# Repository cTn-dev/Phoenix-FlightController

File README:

Flight Controller implementation using Teensy 3.0 as "brain".

PIN setup
I2C SCL - 19
I2C SDA - 18

Rotor 1 - 22
Rotor 2 - 23
Rotor 3 - 9
Rotor 4 - 10

Orientation lights - 14
Battery monitor - 15

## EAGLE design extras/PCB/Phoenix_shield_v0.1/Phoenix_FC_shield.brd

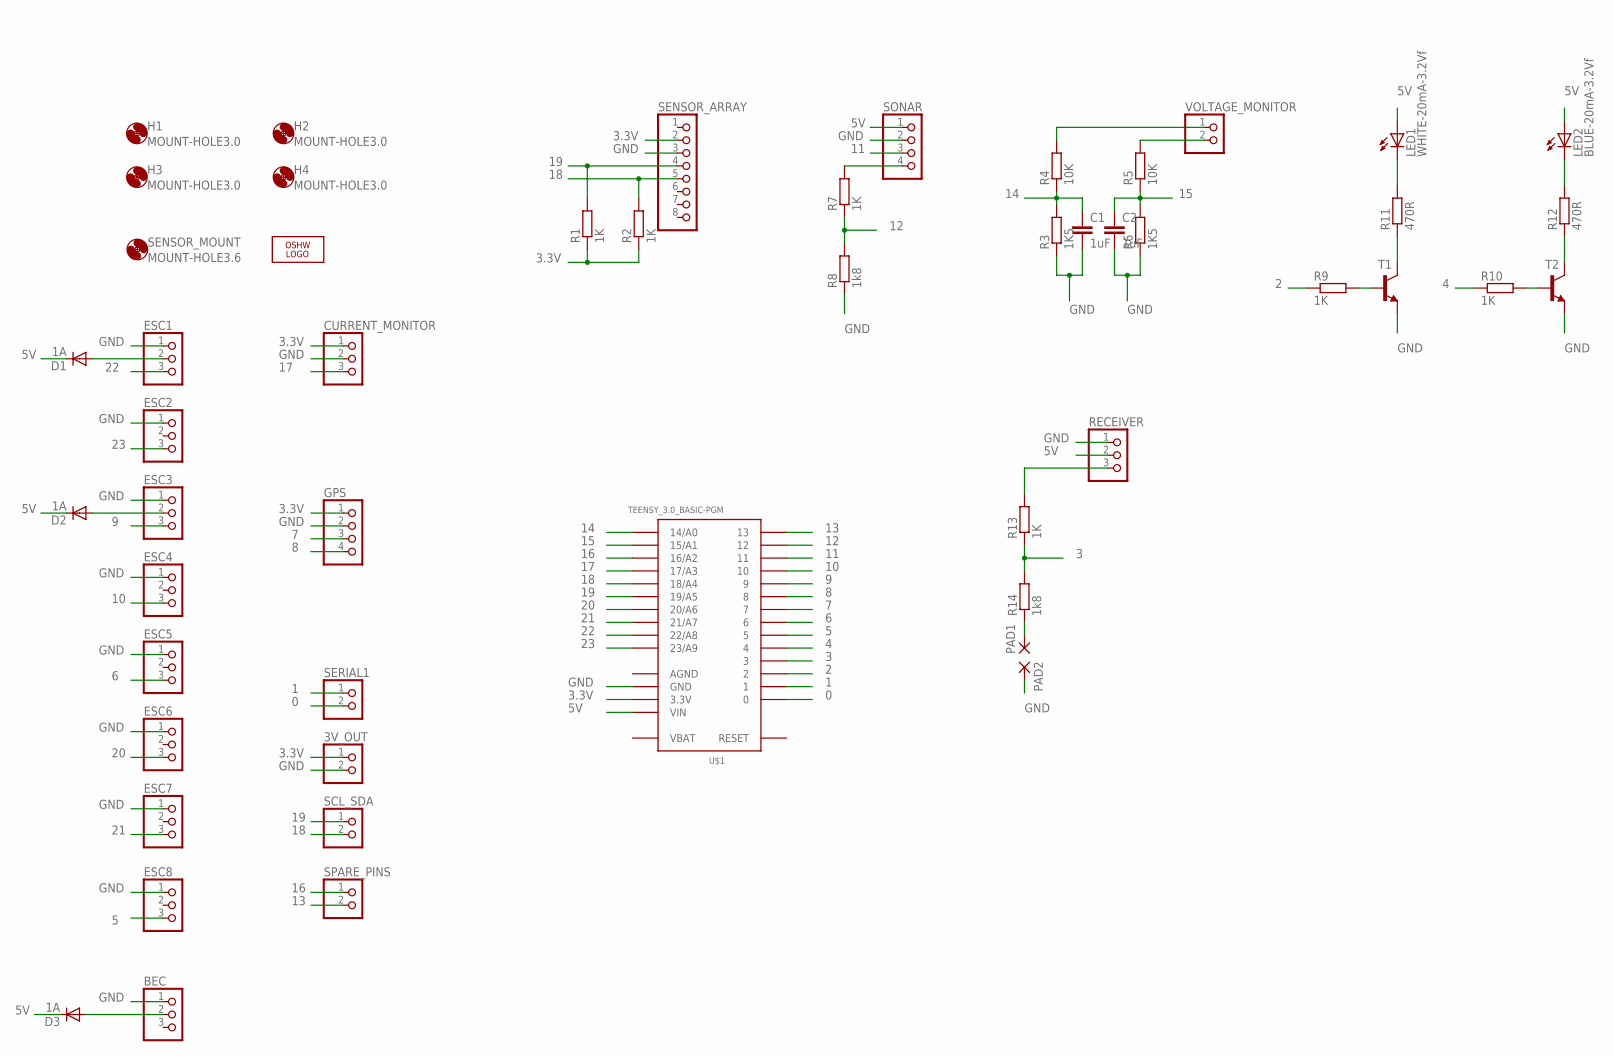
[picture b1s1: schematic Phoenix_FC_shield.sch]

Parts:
3V_OUT: PINHD-1X2; 1X02
BEC: PINHD-1X3; 1X03
C1, C2: 1uF; C0805
CURRENT_MONITOR: PINHD-1X3; 1X03
D1, D2, D3: 1A; DO-214AC
ESC1, ESC2, ESC3, ESC4, ESC5, ESC6, ESC7, ESC8: PINHD-1X3; 1X03
GPS: PINHD-1X4; 1X04
H1, H2, H3, H4: MOUNT-HOLE3.0; 3,0
LED1: WHITE-20mA-3.2Vf; CHIP-LED0805
LED2: BLUE-20mA-3.2Vf; CHIP-LED0805
LOGO1: OSHW_LOGO_8MILX0200-NT; OSHW_8X200_NOTEXT
PAD1, PAD2: WIREPADSMD1,27-254; SMD1,27-2,54
R1, R2, R7, R9, R10, R13: 1K; R0805
R3, R6: 1K5; R0805
R4, R5: 10K; R0805
R8, R14: 1k8; R0805
R11, R12: 470R; R0805
RECEIVER: PINHD-1X3; 1X03
SCL_SDA: PINHD-1X2; 1X02
SENSOR_ARRAY: PINHD-1X8; 1X08
SENSOR_MOUNT: MOUNT-HOLE3.6; 3,6
SERIAL1: PINHD-1X2; 1X02
SONAR: PINHD-1X4; 1X04
SPARE_PINS: PINHD-1X2; 1X02
T1, T2: BC817-40SMD; SOT23-BEC
U$1: TEENSY_3.0_BASIC-PGM
VOLTAGE_MONITOR: PINHD-1X2; 1X02

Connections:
0: SERIAL1.2, U$1.0
1: SERIAL1.1, U$1.1
2: R9.1, U$1.2
3: R13.1, R14.2, U$1.3
3.3V: 3V_OUT.1, CURRENT_MONITOR.1, GPS.1, R1.1, R2.1, SENSOR_ARRAY.2, U$1.3.3V, U$1.3.3V1 (3.3V)
4: R10.1, U$1.4
5: ESC8.3, U$1.5
5V: D1.C, D2.C, D3.C, LED1.A, LED2.A, RECEIVER.2, SONAR.1, U$1.VIN
6: ESC5.3, U$1.6
7: GPS.3, U$1.7
8: GPS.4, U$1.8
9: ESC3.3, U$1.9
10: ESC4.3, U$1.10
11: SONAR.3, U$1.11
12: R7.1, R8.2, U$1.12
13: SPARE_PINS.2, U$1.13
14: C1.1, R3.2, R4.1, U$1.14/A0
15: C2.1, R5.1, R6.2, U$1.15/A1
16: SPARE_PINS.1, U$1.16/A2
17: CURRENT_MONITOR.3, U$1.17/A3
18: R2.2, SCL_SDA.2, SENSOR_ARRAY.5, U$1.18/A4
19: R1.2, SCL_SDA.1, SENSOR_ARRAY.4, U$1.19/A5
20: ESC6.3, U$1.20/A6
21: ESC7.3, U$1.21/A7
22: ESC1.3, U$1.22/A8
23: ESC2.3, U$1.23/A9
AGND: U$1.AGND
GND: 3V_OUT.2, BEC.1, C1.2, C2.2, CURRENT_MONITOR.2, ESC1.1, ESC2.1, ESC3.1, ESC4.1, ESC5.1, ESC6.1, ESC7.1, ESC8.1, GPS.2, PAD2.1, R3.1, R6.1, R8.1, RECEIVER.1, SENSOR_ARRAY.3, SONAR.2, T1.E, T2.E, U$1.GND, U$1.GND1 (GND)
unnamed: R5.2, VOLTAGE_MONITOR.2
unnamed: R7.2, SONAR.4
unnamed: R11.1, T1.C
unnamed: R9.2, T1.B
unnamed: D2.A, ESC3.2
unnamed: PAD1.1, R14.1
unnamed: R4.2, VOLTAGE_MONITOR.1
unnamed: R10.2, T2.B
unnamed: R12.1, T2.C
unnamed: LED1.C, R11.2
unnamed: LED2.C, R12.2
unnamed: D1.A, ESC1.2
unnamed: R13.2, RECEIVER.3
unnamed: BEC.2, D3.A
VBAT: U$1.VBAT

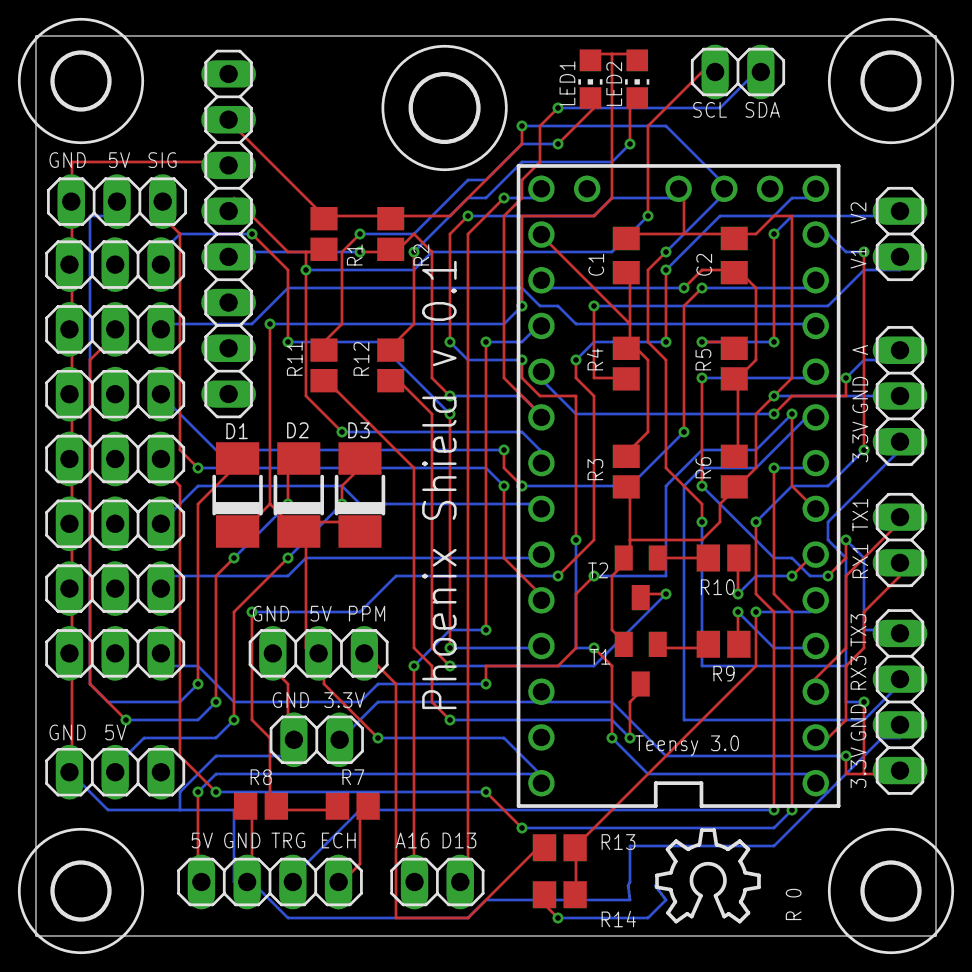
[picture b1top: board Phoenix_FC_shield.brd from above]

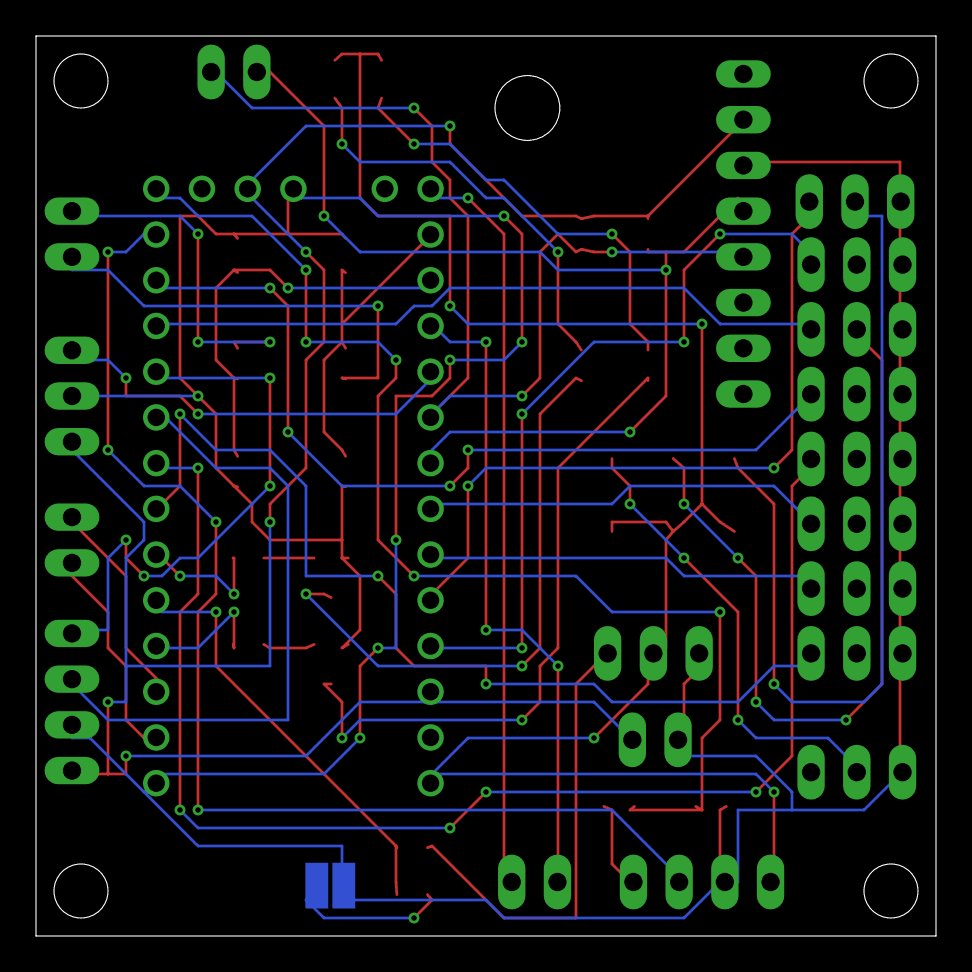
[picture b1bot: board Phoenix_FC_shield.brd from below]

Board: 2 copper layers, 50.0 x 50.0 mm, 51 parts (2 on the bottom side), 41 nets.

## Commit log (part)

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2012-12-16 auto disarm after throttle reaches 1000us (0)
2012-12-16 cleaning up
2012-12-16 more cleanup
2012-12-16 Manual accel offset calibration
2012-12-17 BIG changes to the sensor data handling
    did a rather long flight test, everything seems to be running smooth
2012-12-19 orientation lights & status support
2012-12-20 Added accel scale factor
2012-12-20 bias calculations
2012-12-20 cut off tunings
2012-12-21 readme update
2012-12-21 YAW angle build up "speed up"
2012-12-22 Battery monitor code cleanup + documentation
2012-12-22 temporary disabling battery monitor
    (till the new current sensor arrives)
2012-12-23 cleanup & YAW stick angle speed up
2012-12-23 typo fix
2012-12-24 debugging for ARG
2012-12-24 Critical Readme updates
2012-12-25 readme updates
2012-12-25 optimizations & polish
2012-12-27 optimizations
2012-12-27 mpu documentation header
2012-12-27 pre-baro changes
2012-12-27 altitude hold support
2012-12-27 throttle panic support
2012-12-28 data visualization
2012-12-28 visualization polish
    According to data visualization it seems there is still some improvement
    regarding accel fusion in kinematics
2012-12-29 Lowered accelerometer weight in CMP
2012-12-30 full support for RX visualization
2012-12-31 also output PPM_error with graph data
2013-01-03 accelerometer angle flip corrections
2013-01-03 lots of changes (in the graph area)
2013-01-04 UI polish and 3D visualization
2013-01-04 kinematicsZ PI normalization and YAW corrections
2013-01-05 differen't approach to improve sensor fusion
2013-01-06 DCM kinematics implementation
2013-01-06 YAW fixes
2013-01-06 support for hexa and octo in flex0
2013-01-08 sonar integration (untested)
2013-01-08 IMPORTANT baro and sonar fixes
2013-01-09 partial commit introducing configuration file
2013-01-09 finally dividing sensors into separate libraries
2013-01-09 motor pin setup order change (for clarity)
2013-01-10 moving rx failsafe to the main contoller file
2013-01-10 initial register support for older sensors
2013-01-10 baro/sonar PID changes
    Baro and sonar now uses different PIDs, also by disabling baro/sonar the
    PID objects are removed which helps reduce sketch size on older
    platforms
2013-01-11 new folder structure
2013-01-11 object oriented i2c sensor base
    srf04 isn't part of this sensor array
2013-01-11 improvements in the JS area
2013-01-11 YAW angle flip bugfix
2013-01-11 made the PID throttle correction range bigger
    still requires PID tuning, but its getting there
2013-01-13 PID changes @ I2C timeout testing
2013-01-14 some improvements, serial handling class tomorrow
2013-01-15 initial Ublox commit & mpu6050 i2c bypass
2013-01-16 i2c scanner in extras folder
2013-01-16 initial MS5611 sensor support (not working yet)
2013-01-17 proper HMC5883L support
2013-01-17 GPS polishing
2013-01-18 scale factor update
2013-01-19 3D visualization bugfixes
2013-01-19 full battery monitor current support
2013-01-19 accel calibration
2013-01-20 polish & optimizing
2013-01-21 new sensor data storage structure (array based)
    also all kinematics now take sensor data via priority
    gyro => accel => mag => gps = > magic genie
2013-01-21 some notes from kha
2013-01-24 ARG fixes
2013-01-26 optimization & documentation
2013-01-26 gyro calibration sanity checks
2013-01-26 multiple frames related changes
2013-01-27 ADXL345 & ITG3200 support
2013-01-27 polishing
2013-01-27 cleanup
2013-01-27 tiny cleanup
2013-01-28 bugfix
2013-01-30 faster baro response
    (this is still in testing, i am having some serious problems testing the
    baro alt hold indoors)
2013-01-30 typo fix and support for some basic OFF ON defines
2013-02-01 more EEPROM support
2013-02-01 Adding support to ACCEL on dataStorage, fixing some indentation problems on ACCEL as well. Changed dataStorage include position so it can be accessed on other included files.
2013-02-01 small type change
2013-02-01 3,4,6,8 motor setup for teensy hw
2013-02-01 some alpha stage configurator communication code
2013-02-01 "initial" alpha configurator comit
2013-02-02 working esc calibration
2013-02-02 some changes from karis brain
2013-02-03 configurator protocol improvements
2013-02-03 configurator up
2013-02-03 command log for configurator
2013-02-03 more work on the configurator
2013-02-04 more work on configurator
2013-02-05 cleaning up, optimizing, sanitizing serial com
2013-02-05 improvements on the serial com side
2013-02-06 initial switch to "ublox" style protocol
2013-02-06 data com between FC and config via custom PTC
2013-02-07 tiny bugfixes for the configurator tab ui
2013-02-07 configurator improvements
2013-02-07 RX graph implemented
2013-02-08 some minor PID value changes
2013-02-08 vehicle view (2 axis) implemented
2013-02-08 second configurator cleanup, RX graph legend
2013-02-09 accel calibration handler
    both front end and back end are ready, however there is an Z axis
    calibration fix required (thats yet to be implemented)
2013-02-09 announced Z axis calibration fix
2013-02-09 accelerometer calibration fixes
    seems to be perfect =)
2013-02-09 6DOF mpu stick fixes
2013-02-09 optimizing serial com side
2013-02-09 fixing some documentation
2013-02-10 configurator motor output implemented
2013-02-10 support for flexible configuration UNION size
2013-02-10 AVR related fixes
2013-02-11 more AVR bugfixes.. oh
2013-02-11 more AVR bugfixes
2013-02-11 tiny AVR related polishing
2013-02-11 ability to re-initialize eeprom data
2013-02-11 main serial bus slowdown for AVR
2013-02-11 esc calibration request bugfix
2013-02-11 implemented invSqrt & disabled pointers to accel
2013-02-12 switching from doubles to floats
    (significant performance boost), invsqrt disabled (untill all of the
    output issues gets resolved)
2013-02-12 polishing for initial configurator page
2013-02-12 GPS PID fields in EEPROM
2013-02-13 tiny strikes in the GPS section
2013-02-14 GPS up
2013-02-14 untested AQ shield 2.0/2.1 defines
2013-02-15 some different motor setup dis-armed fixes
2013-02-15 bugfixes
2013-02-15 yaw support in vehicle view
2013-02-15 lots of bugfixes in the sensor area
2013-02-15 configurator improvement
2013-02-15 configurator readme for linux users
2013-02-17 time bugfixes and cleanup
2013-02-17 configurator readme update
2013-02-18 updating jquery and flotr2 to the latest version
2013-02-18 tiny optimizations in serial com area
2013-02-19 PCB up
2013-02-19 PCB - tiny resistor value changes
2013-02-20 bugfixes related to jDataView removal
2013-02-21 better handling of serial ports in configurator
2013-02-21 mpu6050 10DOF stick critical bugfix
2013-02-23 more flexible tab assignment in configurator
2013-02-23 initial support for channel assignment
2013-02-23 part 3/3 of the channel assignment commit
2013-02-23 polishing last commit
2013-02-24 re-globaling some variables in configurator
2013-02-24 different alive led state handling
2013-02-25 corrected spacing
2013-02-25 polished graph legends in configurator
2013-02-26 configurator visual upgrade
2013-02-27 configurator polishing
2013-02-28 stronger weight for accelerometer fusion
2013-03-01 updating some pilot processor documentation
2013-03-02 the long awaited YAW fix for CMP kinematics
2013-03-02 cleaning up CMP kinematics a little
2013-03-03 adding MAF filter to the extras folder
2013-03-03 optimizing motor output in serial com
2013-03-03 initial configurator code for motor commands
    inspired by Shadow6363
2013-03-04 finishing touches to motor command handling
2013-03-04 optimizing hardcoded stuff in ESC calibration
2013-03-05 improving LED status support
2013-03-06 pre-comit to generalize CHANNELS
2013-03-06 enhanced RX failsafe routine from kha
2013-03-06 reverting unnecessary PPM code changes
2013-03-12 polishing teensy 3.0 receiver code
2013-03-15 manual accelerometer offset tuning support
    feature proposed by ReadError
2013-03-16 fixing some precompiler indentation
2013-03-16 configurator eeprom version checking
2013-03-16 data storage documentation
2013-03-18 minimum armed throttle support (FC, configurator)
2013-03-18 optimizing some configurator stuff
2013-03-20 adding some magnetometer required calculations
2013-03-20 magnetometer code improvements
2013-03-25 Revert "experimental gyroscope overtime bias calibration"
    This reverts commit 199bb3f501250914fb9043802a42de9171bc3439.
2013-03-27 updating flotr2
2013-03-31 optimizing PID initialization (visual only)
2013-03-31 cleaning up/optimizing configurator
2013-04-02 some ms5611 baro implementation changes
2013-04-03 initial commit for "alive" sensor detection
2013-04-04 configurator UI polish + some sensor bugfixes
2013-04-04 polishing some of the sensor libraries
2013-04-05 configurator about page update
2013-04-10 bugfix for AVR
2013-04-10 port usage indicator
2013-04-10 crc failed response and send union working
2013-04-10 CRC checking both ways (mostly working)
    FC side of the protocol needs refactoring
2013-04-11 almost done (cleanup required)
2013-04-11 MCU PSP cleanup done
2013-04-13 MCU side for sending mag and baro data
2013-04-14 optimizing MCU serial side a little
2013-04-14 vehicle view moved to the new data structure
2013-04-14 receiver moved to the new data structure
2013-04-14 motor command & accel calibration moved
2013-04-14 plot initialization bugfixes
2013-04-15 polishing a little
2013-04-18 adding buddy of mine to the contributor list
2013-04-20 more work on dynamic AUX functions
2013-04-20 making room for AUX tab, also initializing files
2013-04-20 correcting failsafe functionality with new AUX
2013-04-20 realtime AUX trigger indicator
2013-04-20 adding some info for AUX and polishing UI
2013-04-20 failsafe improvements
2013-04-20 documentation
2013-04-21 polishing/fixing some gps code
2013-04-21 speeding up YAW buildup
2013-04-21 fixing reverted pitch
    TX settings needs to be adjusted for this
2013-04-21 ublox module "alive" detection
2013-04-21 send over all "usable" GPS data
2013-04-21 GPS backend for configurator
2013-04-22 GPS heading visualization
2013-04-22 polishing/improving GPS parser
2013-04-23 Revert "optimized handling of "FAST" YAW commands"
    This reverts commit 3bb78803d9d9dd8c8448c6224ebc9d1b4e5daeb1.
2013-05-03 validating some dataStorage code
2013-05-04 retry sanity check for gyro calibrations
2013-05-04 "on the fly" user accelerometer trimming
2013-05-04 optimizations for serialcom side
2013-05-07 adding some new supporters to the list
2013-05-07 polishing serialcom side
2013-05-11 Fully dynamic 16 channel receiver support 1/?
    With this commit, we might be officially forced to drop atmega168/328
    support because of the lack of resources required for the software to
    operate properly (current setup of fully scalable functions for 16
    channel receiver requires usage of 64bit variable for aux mask and
    function masks.
    This will most likely be "too much" for the 2KB of ram available on the
2013-05-11 Fully dynamic 16 channel receiver support 2/?
2013-06-01 polishing accelerometer TX trimming functionality
2013-06-09 backup/restore feature in configurator
2013-06-10 stronger validation of restore file
2013-06-12 updating jquery to v2.0.2
2013-06-18 getting the 16 channel PPM support in order
    receiver code should now properly handle 4/6/8/16 channel receivers,
    with PPM sync pulse set to 2.5ms > by default
2013-06-18 tiny sync PPM value fix for atmega
2013-06-19 workaround for onClosed and open PORT
2013-06-20 removing some left over variables
2013-06-20 initializing rest of the bits to 0 (for safety)
2013-06-20 initial wrapper & files for sensor mapping
2013-06-21 sensor mapping implementation in configurator
2013-06-21 re-distributed axis mapping to all gyroscopes
2013-06-21 re-distributed axis mapping to magnetometer
2013-07-02 workaround for "bouncy" landing
2013-07-02 Properly refresh UI after EEPROM restore
2013-07-09 nicer approach to resolve too long messages
2013-07-11 removing old code
2013-07-30 updating jquery to the latest version
2013-11-25 adding jquery map file
2017-01-04 actually check if Size variable is larger than MAF_ARRAYSIZE
2017-01-04 rename smoothFactor to buffer_size to give it a more meaningful name
